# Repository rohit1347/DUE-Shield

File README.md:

# DUE-Shield
PCB for Cognitive Switching Center (CSC) based on Arduino DUE.

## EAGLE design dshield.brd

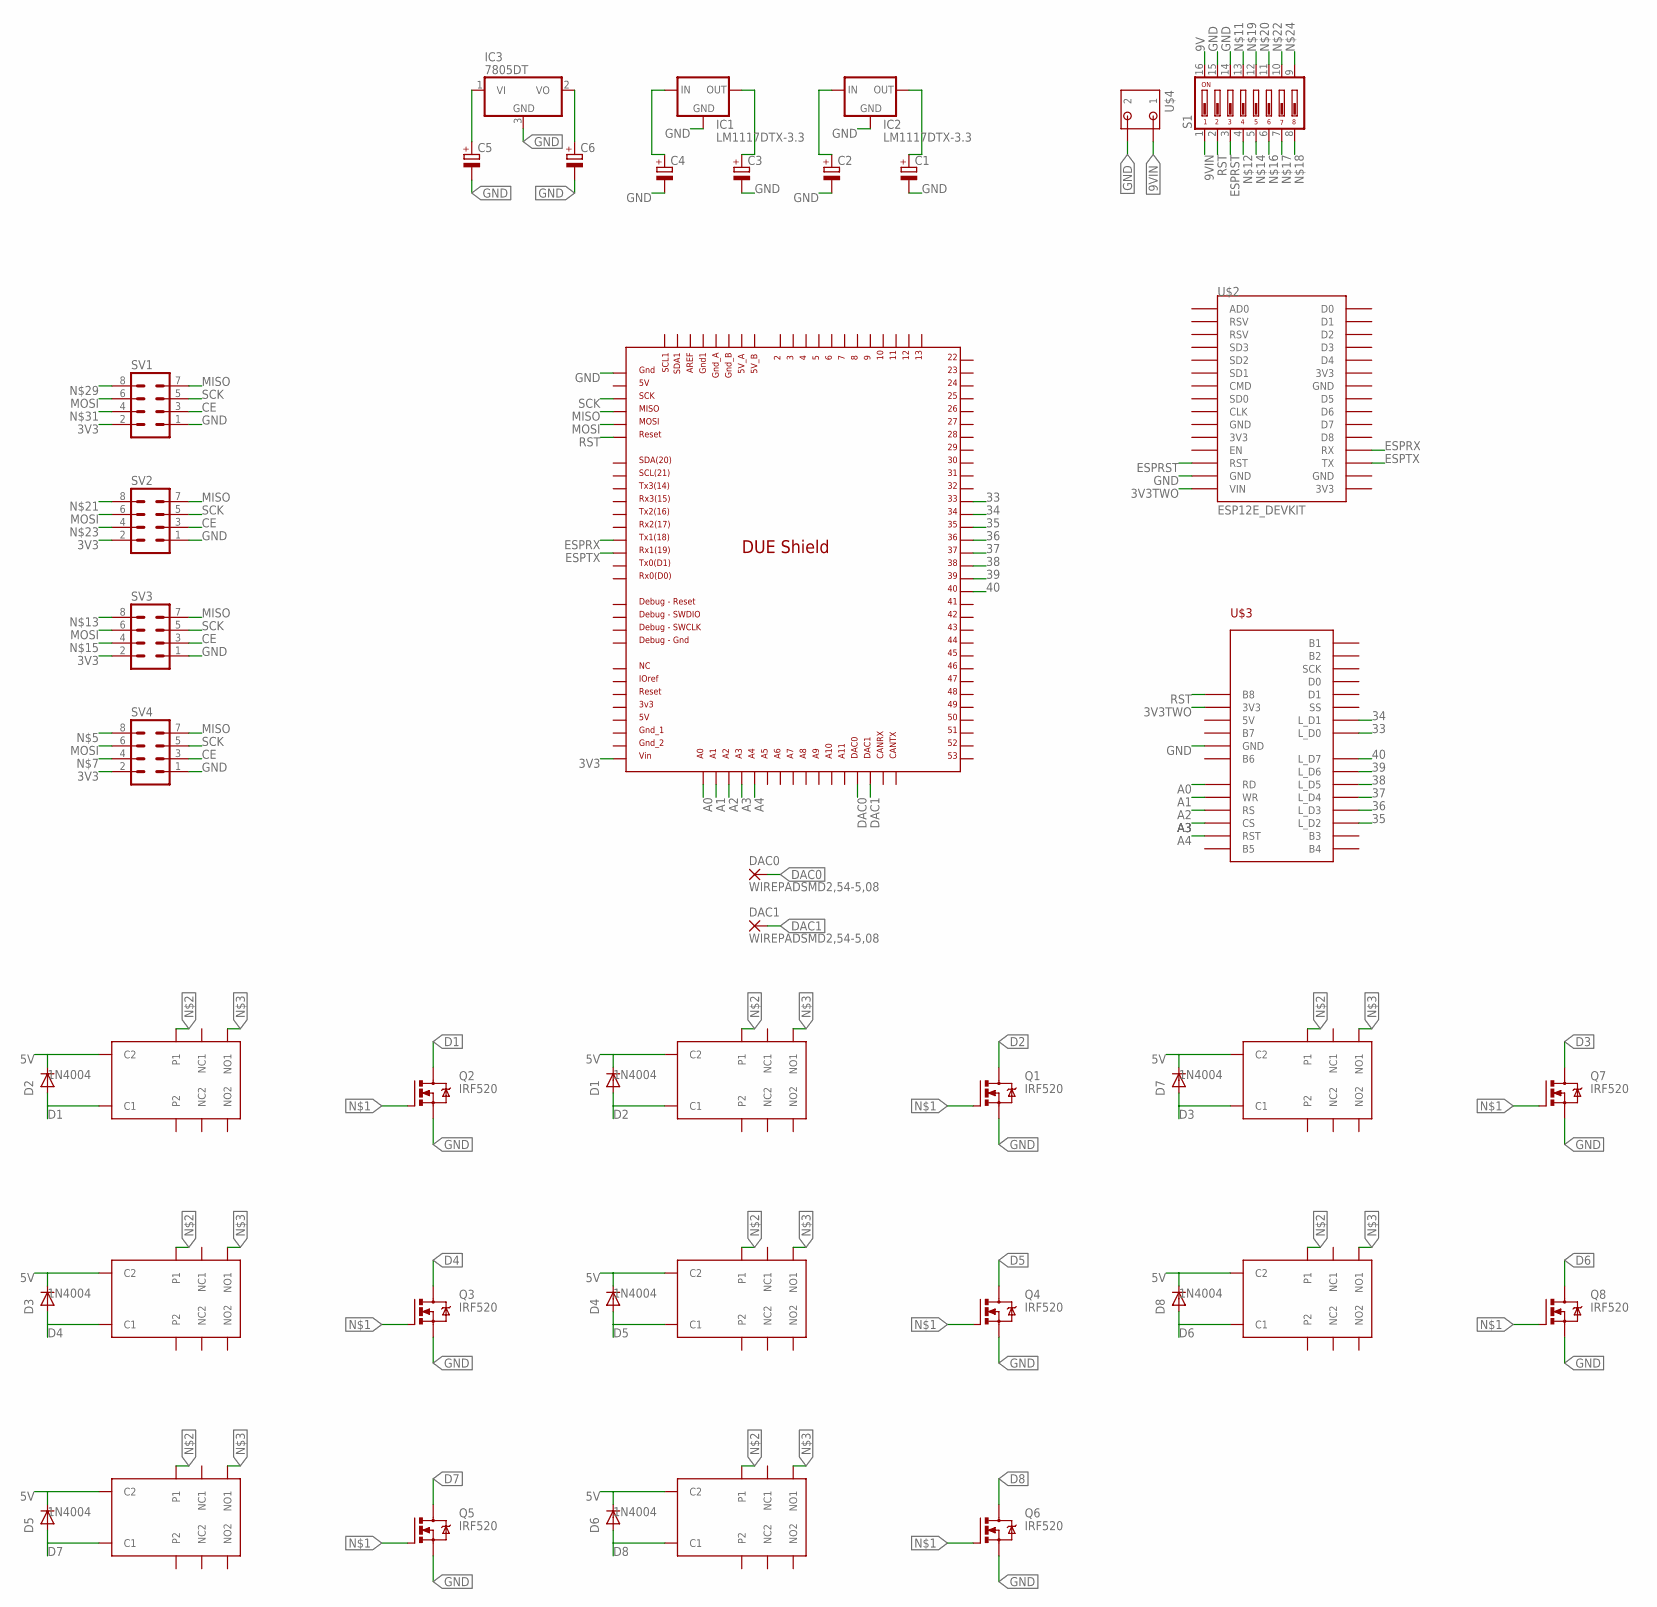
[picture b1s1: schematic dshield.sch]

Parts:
BTPL1, BTPL2, BTPL3, BTPL4, BTPL5, BTPL6, BTPL7, BTPL8: GS-SH-2XXT; G_RELAY_SMD
C1, C2, C3, C4, C5, C6: CPOL-EUE2.5-6; E2,5-6
D1, D2, D3, D4, D5, D6, D7, D8: 1N4004; DO41-10
DAC0, DAC1: WIREPADSMD2,54-5,08; SMD2,54-5,08
IC1, IC2: LM1117DTX-3.3; TO252
IC3: 7805DT; TO252
Q1, Q2, Q3, Q4, Q5, Q6, Q7, Q8: IRF520; TO220BV
S1: DS08; DS-08
SV1, SV2, SV3, SV4: MA04-2
U$1: DUE(NORMAL)
U$2: ESP12E_DEVKIT
U$3: SPFD5408
U$4: SPTBB2-A2; SPTB

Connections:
3V3: C3.+, IC1.TAB (OUT), SV1.2, SV2.2, SV3.2, SV4.2, U$1.VIN
3V3TWO: C1.+, IC2.TAB (OUT), U$2.VIN, U$3.3V3
5V: BTPL1.C2, BTPL2.C2, BTPL3.C2, BTPL4.C2, BTPL5.C2, BTPL6.C2, BTPL7.C2, BTPL8.C2, C6.+, D1.C, D2.C, D3.C, D4.C, D5.C, D6.C, D7.C, D8.C, IC3.2 (VO)
9V: C2.+, C4.+, C5.+, IC1.2 (IN), IC2.2 (IN), IC3.1 (VI), S1.16
9VIN: S1.1, U$4.B2 (1)
33: U$1.33, U$3.L_D0
34: U$1.34, U$3.L_D1
35: U$1.35, U$3.L_D2
36: U$1.36, U$3.L_D3
37: U$1.37, U$3.L_D4
38: U$1.38, U$3.L_D5
39: U$1.39, U$3.L_D6
40: U$1.40, U$3.L_D7
A0: U$1.A0, U$3.RD
A1: U$1.A1, U$3.WR
A2: U$1.A2, U$3.RS
A3: U$1.A3, U$3.CS
A4: U$1.A4, U$3.RST
CE: SV1.3, SV2.3, SV3.3, SV4.3
D1: BTPL2.C1, D2.A, Q2.D
D2: BTPL1.C1, D1.A, Q1.D
D3: BTPL7.C1, D7.A, Q7.D
D4: BTPL3.C1, D3.A, Q3.D
D5: BTPL4.C1, D4.A, Q4.D
D6: BTPL8.C1, D8.A, Q8.D
D7: BTPL5.C1, D5.A, Q5.D
D8: BTPL6.C1, D6.A, Q6.D
DAC0: DAC0.1, U$1.DAC0
DAC1: DAC1.1, U$1.DAC1
ESPRST: S1.3, U$2.RST
ESPRX: U$1.TX1, U$2.RX
ESPTX: U$1.RX1, U$2.TX
GND: C1.-, C2.-, C3.-, C4.-, C5.-, C6.-, IC1.1 (GND), IC2.1 (GND), IC3.3 (GND), Q1.S, Q2.S, Q3.S, Q4.S, Q5.S, Q6.S, Q7.S, Q8.S, S1.14, S1.15, SV1.1, SV2.1, SV3.1, SV4.1, U$1.5V_ICSP, U$2.GND@1 (GND), U$3.GND, U$4.A2 (2)
MISO: SV1.7, SV2.7, SV3.7, SV4.7, U$1.MISO_ICSP
MOSI: SV1.6, SV2.6, SV3.6, SV4.6, U$1.MOSI_ICSP
unnamed: Q1.G, Q2.G, Q3.G, Q4.G, Q5.G, Q6.G, Q7.G, Q8.G
unnamed: BTPL1.P1, BTPL2.P1, BTPL3.P1, BTPL4.P1, BTPL5.P1, BTPL6.P1, BTPL7.P1, BTPL8.P1
unnamed: BTPL1.NO1, BTPL2.NO1, BTPL3.NO1, BTPL4.NO1, BTPL5.NO1, BTPL6.NO1, BTPL7.NO1, BTPL8.NO1
RST: S1.2, U$1.RESET_ICSP, U$3.B8
SCK: SV1.5, SV2.5, SV3.5, SV4.5, U$1.SCK_ICSP

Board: 2 copper layers, 44 parts (11 on the bottom side), 40 nets, no tracks yet.
